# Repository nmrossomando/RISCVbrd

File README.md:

RISC-V Test Board
=================

An experiment in RISC-V, powered by (to my knowledge) the only easily purchasable RISC-V chip at the moment, the [SiFive FE310-G000.](https://www.crowdsupply.com/sifive/hifive1)
It is an odd and clearly somewhat experimental chip in its own right, but it is plenty good enough for the puposes of this little project.

License
-------
See the LICENSE file for full details.

Copyright 2018 nmrossomando

Licensed under the Apache License, Version 2.0 (the "License"); you may not use this design except in compliance with the License. You may obtain a copy of the License [here](www.apache.org/licenses/LICENSE-2.0) or in the LICENSE file of this repository.

Unless required by applicable law or agreed to in writing, software distributed under the License is distributed in an "AS IS" BASIS, WITHOUT WARRANTIES OR CONDITIONS OF ANY KIND, either express or implied. See the License for the specific language governing permissions and limitations under the license.

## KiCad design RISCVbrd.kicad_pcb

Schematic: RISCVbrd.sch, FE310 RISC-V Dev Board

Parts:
C1, C4: 10nF; C_0603_1608Metric
C2, C3, C5, C6, C7, C8, C9, C10, C11: 100nF; C_0603_1608Metric
C12: 10uF; C_1206_3216Metric
C13, C16: 16pF; C_0603_1608Metric
C14, C19, C23: 100nF; C_0805_2012Metric
C15: 10nF; C_0805_2012Metric
C17, C18, C20, C21, C22: 1uF; C_0805_2012Metric
D1: Green; LED_0805_2012Metric
J1, J2: Conn_01x14; PinSocket_1x14_P2.54mm_Vertical
J3: Power; TerminalBlock_TE_282834-2_1x02_P2.54mm_Horizontal
J4: JTAG Header; PinHeader_2x05_P2.54mm_Vertical
LOGO1: LOGO; DRAGON
Q1: DMN63D8LDW; SOT-363_SC-70-6_Handsoldering
Q2: DMG2305UX; SOT-23
R1: 100; R_0603_1608Metric
R2, R3, R6: 100k; R_0805_2012Metric
R4: 300; R_0805_2012Metric
R5: 1k; R_0805_2012Metric
R7: 100k; R_0603_1608Metric
RN1: 100k; R_Array_Concave_4x0402
SW1, SW2: SW_Push; SW_PUSH_6mm_H4.3mm
U1: FE310-G000; QFN-48-1EP_6x6mm_P0.4mm_EP4.3x4.3mm
U2: 74LVC2G07; SOT-23-6
U3: S25FL; WSON8L-WNG008
U4: MIC5504-1.8YM5; SOT-23-5
U5: MIC5504-3.3YM5; SOT-23-5
U6: ADC104S021; MSOP-10_3x3mm_P0.5mm
Y1: 16MHz; Crystal_SMD_3225-4Pin_3.2x2.5mm

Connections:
+1V8: C1.1, C2.1, C3.1, C5.1, C7.1, C14.1, C20.1, J1.1, R1.2, R2.1, R6.1, U1.6, U1.19, U1.23, U1.30, U1.46, U2.5, U4.5 (VOUT)
+3.3VADC: C22.1, C23.1, Q2.3, U6.2
+3V3: C4.1, C6.1, C9.1, C11.1, C19.1, C21.1, J2.1, J4.4, Q2.2, R3.1, R7.1, RN1.6, RN1.7, RN1.8, U1.11, U1.12, U1.32, U1.47, U3.8, U5.5
ADC_CUT: Q1.5, U1.17
AIN1: J1.14, U6.7
AIN2: J1.13, U6.6
AIN3: J1.12, U6.5
AIN4: J1.11, U6.4
A_CS: RN1.3, U1.27, U6.1
CS2: J1.9, RN1.1, U1.33
CS3: J1.10, RN1.2, U1.34
F_CS: R7.2, U1.5, U3.1
F_D0: U1.4, U3.5
F_D1: U1.3, U3.2
F_D2: U1.2, U3.3
F_D3: U1.1, U3.7
F_SCK: U1.48, U3.6
GND: C1.2, C2.2, C3.2, C4.2, C5.2, C6.2, C7.2, C9.2, C11.2, C12.2, C13.2, C14.2, C15.2, C16.2, C17.2, C18.2, C19.2, C20.2, C21.2, C22.2, C23.2, J1.2, J2.2, J3.2, J4.2, J4.10, Q1.1, Q1.4, R5.1, SW1.1, SW2.1, U1.49, U2.2, U3.4, U4.2 (GND), U5.2, U6.3, Y1.2, Y1.4
GPIO0: J1.4, U1.25
GPIO1: J1.5, U1.26
GPIO11: J2.13, U1.35
GPIO12: J2.12, U1.36
GPIO13: J2.11, U1.37
GPIO18: J2.8, U1.40
GPIO19: J2.7, U1.41
GPIO20: J2.6, U1.42
GPIO21: J2.5, U1.43
GPIO22: J2.4, U1.44
GPIO23: J2.3, U1.45
MISO: J1.7, U1.29, U6.9
MOSI: J1.6, U1.28, U6.8
unnamed: C8.1, C10.1, R1.1, U1.7
unnamed: C8.2, C10.2, U1.8
unnamed: D1.1, Q1.6
unnamed: D1.2, R4.1
unnamed: Q1.3, Q2.1, R3.2
RX: J2.10, U1.38
SCK: J1.8, U1.31, U6.10
SRST: J1.3, J4.6, U2.1
TCK: J4.1, U1.13
TDI: J4.9, U1.16
TDO: J4.3, U1.14
TMS: J4.5, U1.15
TX: J2.9, U1.39
VBUS: C12.1, C17.1, C18.1, J3.1, R4.2, U4.1 (VIN), U4.3 (EN), U5.1, U5.3
WAKE_LED: Q1.2, R5.2, U1.22
XTAL_IN: C13.1, U1.9, Y1.1
XTAL_OUT: C16.1, U1.10, Y1.3
~RESET~: C15.1, R2.2, SW1.2, U1.24, U2.6
~WAKEUP~: R6.2, SW2.2, U1.18, U2.4
~WAKE~: J2.14, U2.3

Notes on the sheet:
MICROCONTROLLER
XTAL
JTAG
RESET LOGIC
FLASH
1.8V REG
3.3V REG
AWAKE LED
WAKEUP LOGIC
ADC
ADC EN
VIN
HEADERS
CS PU

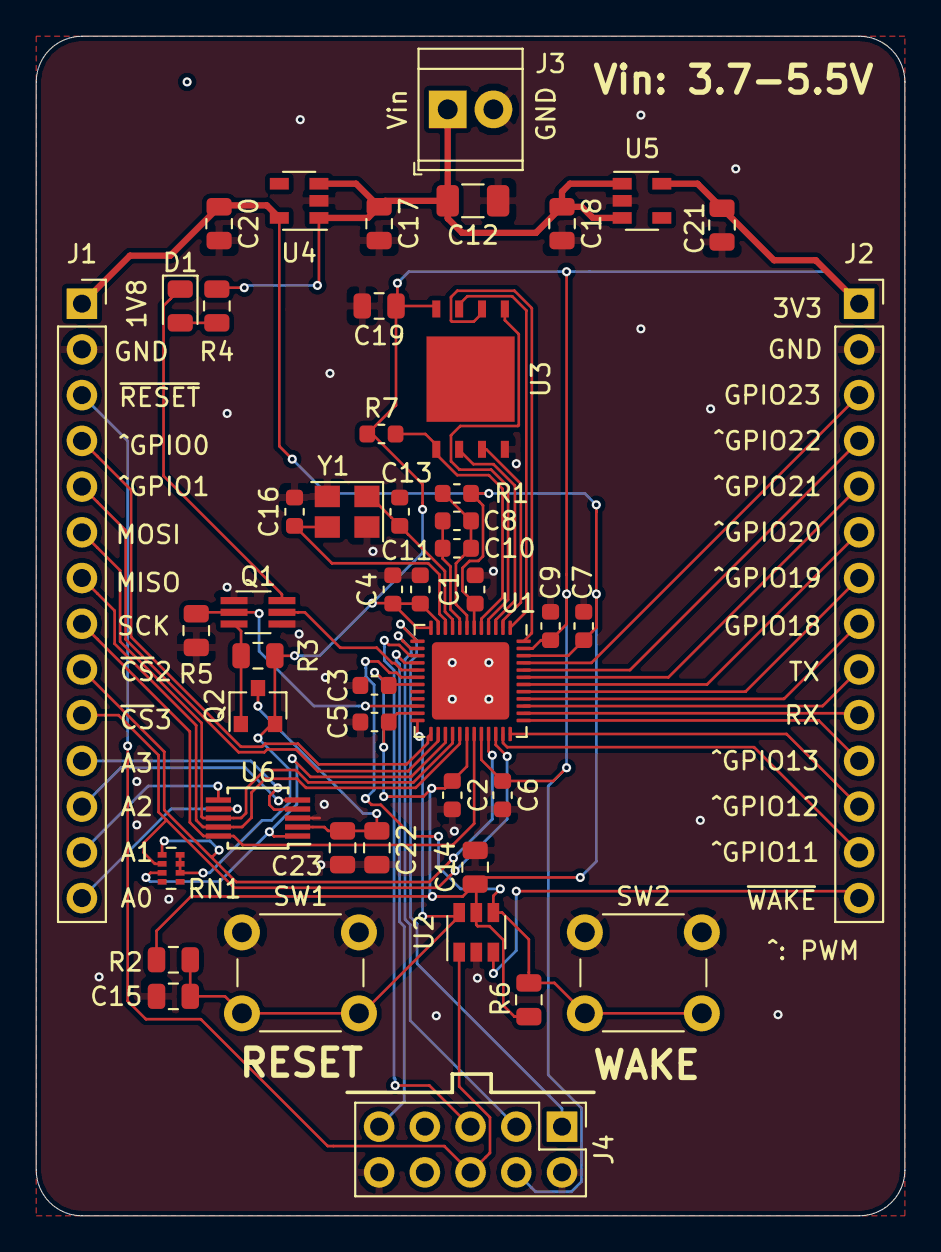
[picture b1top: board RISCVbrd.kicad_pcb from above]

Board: 2 copper layers, 48.3 x 65.5 mm, 48 parts (0 on the bottom side), 51 nets.

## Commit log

2018-09-23 Fixed backwards Q2, decoupling cap values (should have had one 10nF); added pullups on all chip selects.
